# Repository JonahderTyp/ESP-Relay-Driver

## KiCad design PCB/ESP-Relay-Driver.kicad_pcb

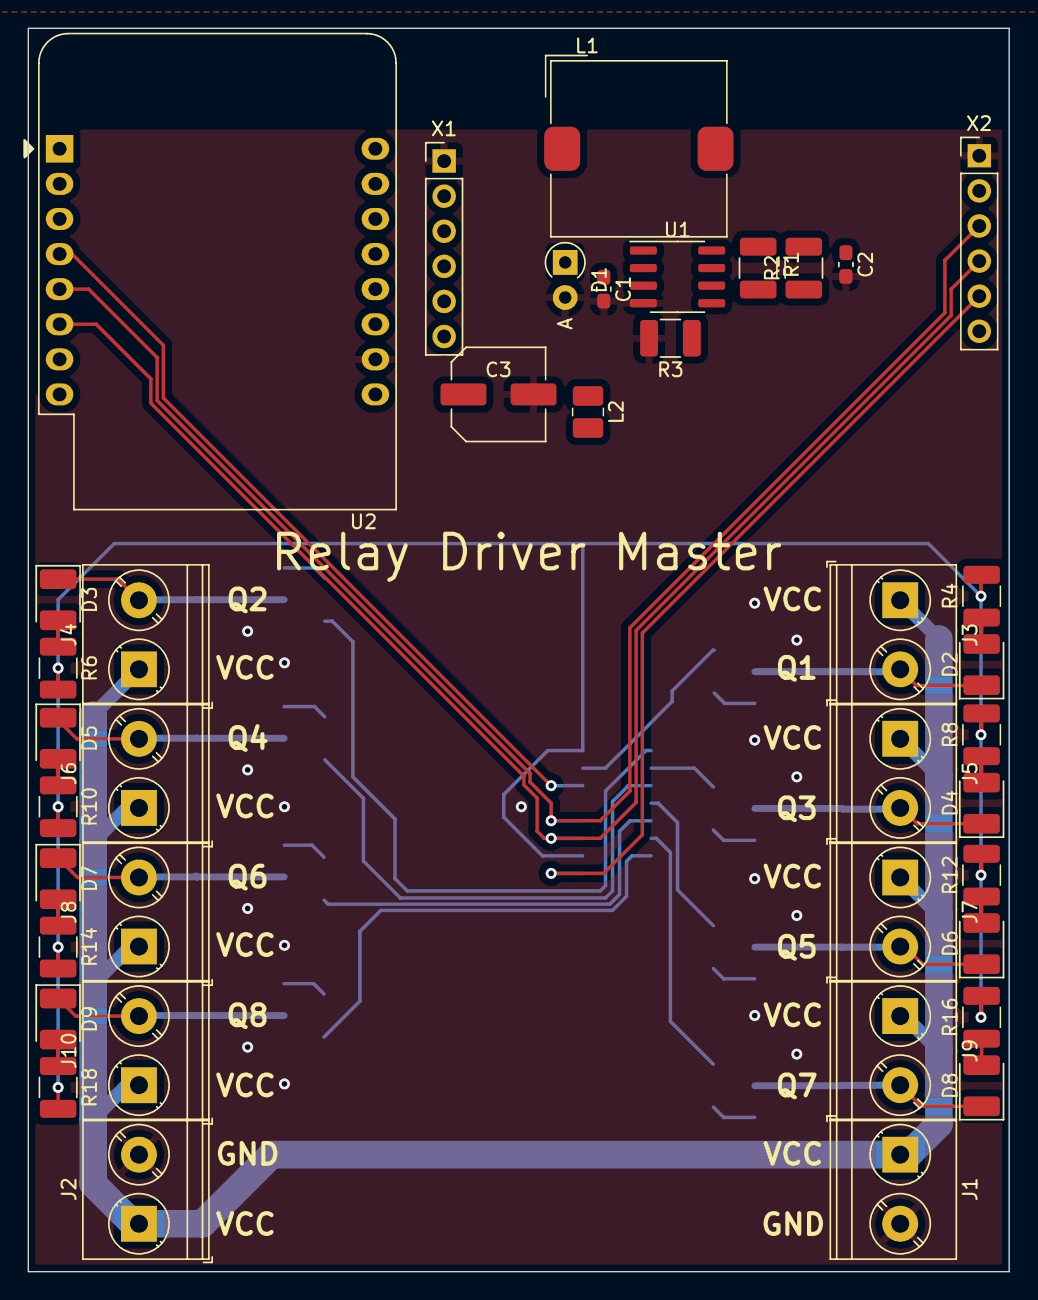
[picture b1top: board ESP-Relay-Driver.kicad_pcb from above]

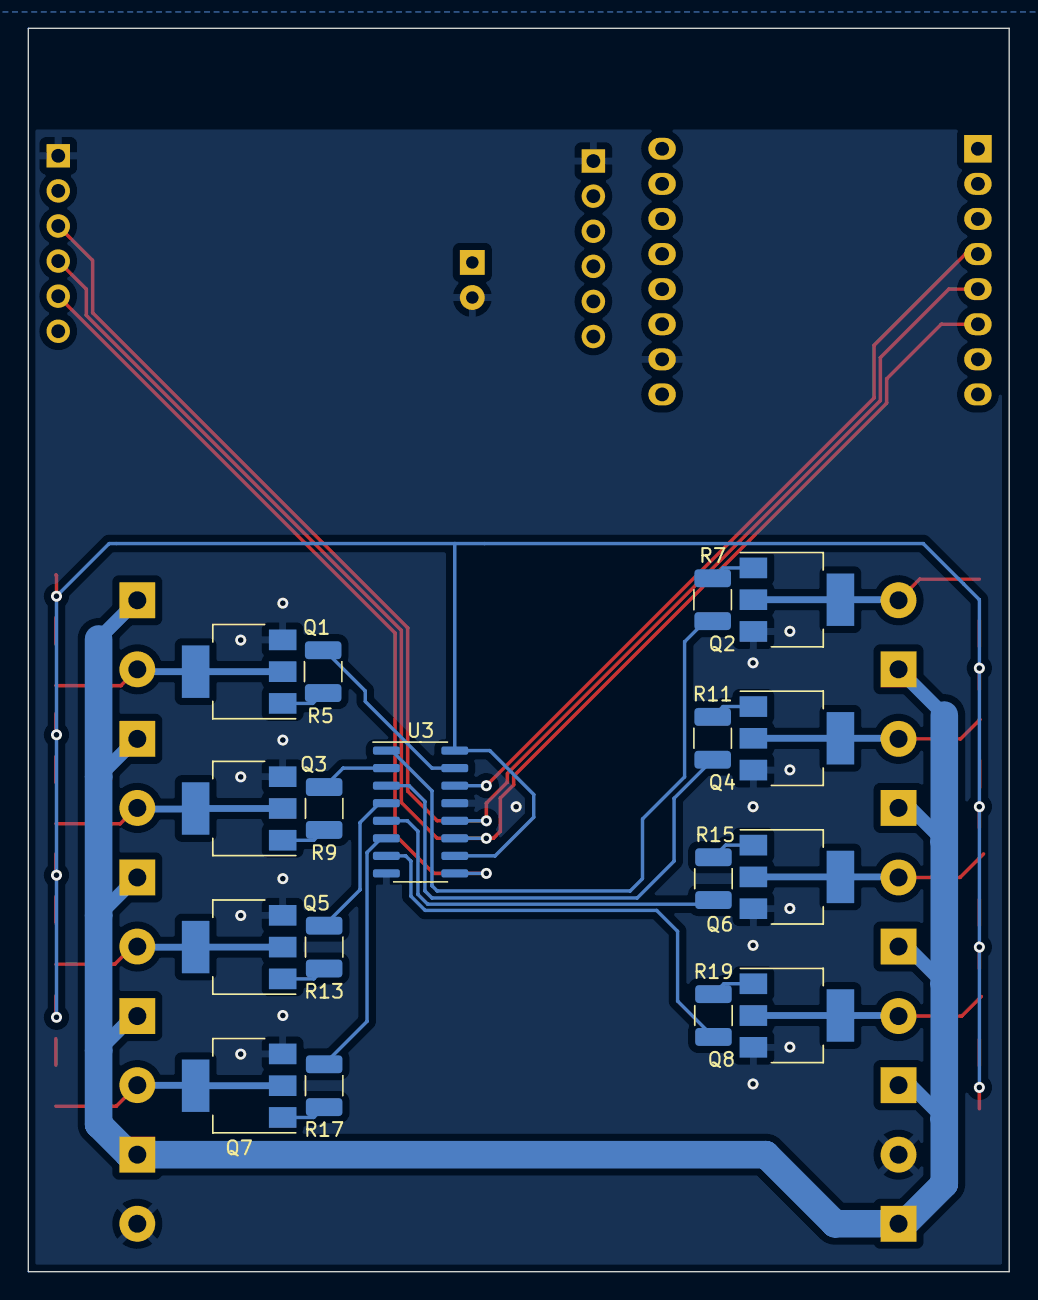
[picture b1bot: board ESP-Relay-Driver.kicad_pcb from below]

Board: 2 copper layers, 71.0 x 90.0 mm, 56 parts (17 on the bottom side), 49 nets.

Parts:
C1: 470p; C_0603_1608Metric_Pad1.08x0.95mm_HandSolder
C2: 470; C_0603_1608Metric_Pad1.08x0.95mm_HandSolder
C3: 100uf; C_Elec_6.3x7.7
D1: 1N5819; D_A-405_P2.54mm_Vertical_AnodeUp
D2, D3, D4, D5, D6, D7, D8, D9: LED; LED_1210_3225Metric_Pad1.42x2.65mm_HandSolder
J1, J2, J3, J4, J5, J6, J7, J8, J9, J10: Conn_01x02; TerminalBlock_Phoenix_PT-1,5-2-5.0-H_1x02_P5.00mm_Horizontal
L1: 220uH; L_TDK_SLF12565
L2: 1uH; L_1008_2520Metric_Pad1.43x2.20mm_HandSolder
Q1, Q2, Q3, Q4, Q5, Q6, Q7, Q8: BCP56; SOT-223-3_TabPin2
R1: 0.33R; R_1210_3225Metric_Pad1.30x2.65mm_HandSolder
R2: 3.6k; R_1210_3225Metric_Pad1.30x2.65mm_HandSolder
R3, R4, R5, R6, R7, R8, R9, R10, R11, R12, R13, R14, R15, R16, R17, R18, R19: 1.2k; R_1210_3225Metric_Pad1.30x2.65mm_HandSolder
U1: MC34063AD; SOIC-8_3.9x4.9mm_P1.27mm
U2: WeMos_D1_mini; WEMOS_D1_mini_light
U3: 74HC595; SOIC-16_3.9x9.9mm_P1.27mm
X1, X2: Conn_01x06_Male; PinHeader_1x06_P2.54mm_Vertical

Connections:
+3.3V: U2.8 (3V3), X1.4
+5V: C3.1, L2.2, R4.2, R6.2, R8.2, R10.2, R12.2, R14.2, R16.2, R18.2, U2.9 (5V), U3.10 (~SRCLR), U3.16 (VCC), X2.2
/ESP_RXD: U2.15 (RX), X1.3
/ESP_TXD: U2.16 (TX), X1.2
/GPIO0: U2.12 (D3), X1.6
/Q1: R5.1, U3.15 (QA)
/Q2: R7.1, U3.1 (QB)
/Q3: R9.1, U3.2 (QC)
/Q4: R11.1, U3.3 (QD)
/Q5: R13.1, U3.4 (QE)
/Q6: R15.1, U3.5 (QF)
/Q7: R17.1, U3.6 (QG)
/Q8: R19.1, U3.7 (QH)
/QH: U3.9 (QH'), X2.5
/RCLK: U2.5 (MISO/D6), U3.12 (RCLK), X2.3
/RST: U2.1 (~RST), X1.5
/SER: U2.4 (SCK/D5), U3.14 (SER)
/SRCLK: U2.6 (MOSI/D7), U3.11 (SRCLK), X2.4
GND: C1.2, C2.2, C3.2, D1.2 (A), J1.2, J2.2, Q1.3 (E), Q2.3 (E), Q3.3 (E), Q4.3 (E), Q5.3 (E), Q6.3 (E), Q7.3 (E), Q8.3 (E), R3.2, U1.4 (GND), U2.10 (GND), U3.8 (GND), U3.13 (~OE), X1.1, X2.1
unnamed: C1.1, U1.3 (TC)
unnamed: C2.1, L1.2, L2.1, R2.2
unnamed: D1.1 (K), L1.1, U1.2 (SwE)
unnamed: D2.1 (K), J3.2, Q1.2 (C)
unnamed: D2.2 (A), R4.1
unnamed: D3.1 (K), J4.2, Q2.2 (C)
unnamed: D3.2 (A), R6.1
unnamed: D4.1 (K), J5.2, Q3.2 (C)
unnamed: D4.2 (A), R8.1
unnamed: D5.1 (K), J6.2, Q4.2 (C)
unnamed: D5.2 (A), R10.1
unnamed: D6.1 (K), J7.2, Q5.2 (C)
unnamed: D6.2 (A), R12.1
unnamed: D7.1 (K), J8.2, Q6.2 (C)
unnamed: D7.2 (A), R14.1
unnamed: D8.1 (K), J9.2, Q7.2 (C)
unnamed: D8.2 (A), R16.1
unnamed: D9.1 (K), J10.2, Q8.2 (C)
unnamed: D9.2 (A), R18.1
unnamed: Q1.1 (B), R5.2
unnamed: Q2.1 (B), R7.2
unnamed: Q3.1 (B), R9.2
unnamed: Q4.1 (B), R11.2
unnamed: Q5.1 (B), R13.2
unnamed: Q6.1 (B), R15.2
unnamed: Q7.1 (B), R17.2
unnamed: Q8.1 (B), R19.2
unnamed: R1.2, U1.1 (SwC), U1.7 (Ipk), U1.8 (DC)
unnamed: R2.1, R3.1, U1.5 (Vfb)
VCC: J1.1, J2.1, J3.1, J4.1, J5.1, J6.1, J7.1, J8.1, J9.1, J10.1, R1.1, U1.6 (Vin)

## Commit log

2023-02-10 uploaded files
